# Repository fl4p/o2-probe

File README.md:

# o2-probe

A buried oxygen probe for compost windrows. It combines an electrochemical
O₂ cell, its potentiostat, a heated membrane, and an STM32 that speaks
Modbus RTU, all on one elongated PCB inside a printed body that is potted at
one end and open to the pile gas at the other.

Measuring O₂ in a pile is mainly a condensation problem. Pore gas is
saturated and a buried probe conducts heat outward, so every surface sits
below the dew point. The cell, however, is rated 15–90 %RH *non-condensing*.
Most of this design exists to keep the membrane dry.

*Right: the assembled probe, with half of the printed one-piece body (the
"monobody") cut away. The board is the 107 mm Rev A layout, as KiCad
exports it in 3D. Parts with no KiCad 3D model are red blocks drawn in by
hand. The cable-end cap is at the bottom. Rebuild it with
`make -C cad readme-render`.*

**View the board in the browser:**
[Rev B PCB and schematic in KiCanvas](https://kicanvas.org/?github=https%3A%2F%2Fgithub.com%2Ffl4p%2Fo2-probe%2Ftree%2Fmain%2Fhw%2Frouting%2Frevb-86)

## Status

Research hardware, not a product. A Rev A board runs on the bench and has
been in a pile. Rev B (20 × 86 mm, 2 layers, the ADS1119 replaced by the
STM32's own ADC) is routed and reviewed but not yet fabricated.
`hw/README.md` has the current board state.

## Layout

| path | contents |
|---|---|
| `hw/` | electronics: the KiCad project, its generators (`gen_sch.py` is the schematic's source of truth), audits, routing variants, fab packages, bench logs |
| `hw/firmware/` | STM32G071 firmware (PlatformIO). Its scale factors are generated from `../gen_sch.py` |
| `cad/` | the printed body, head end and fixtures (OpenSCAD), print profiles, the three.js viewer |
| `docs/` | system-level design records: membrane, potting, power, cable, condensation model, calibration budget |
| `model/` | lumped response and heater model (Python, uncalibrated) |
| `analysis/` | calibration and field-error budget scripts |
| `reviews/` | independent design reviews |
| `vendor/` | vendor documents for the membrane |
| `viewer/` | superseded Rev A three.js viewer |

## Where to start

- `docs/PLAN.md` is the system plan and indexes the other design records.
- `hw/DESIGN.md` covers the architecture, I²C address map, register map and
  release gates.
- `hw/firmware/FIRMWARE.md` covers the register map, fault semantics and
  bring-up.
- `docs/O2-CORRECTION-MODEL-BUDGET.md` shows what calibration can and cannot
  buy.
- `cad/README.md` covers the mechanical parts and how to build them.

## History

The electronics and firmware were developed in a separate monorepo and moved
here on 2026-11-02 with their history intact (`hw/`). Before that, this repo's
root held an older, frozen copy of the KiCad project. That copy was removed,
and git history still has it.

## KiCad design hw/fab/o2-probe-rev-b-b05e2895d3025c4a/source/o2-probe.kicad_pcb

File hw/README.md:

# o2-probe

Current Rev B PCB work is in
[`routing/revb-86/o2-probe.kicad_pcb`](routing/revb-86/o2-probe.kicad_pcb).
It uses the current 83-component schematic: AP63203 supplies 3.3 V, R32 filters
the analog rail, REF3425 supplies the reference, and the STM32 ADC replaces
ADS1119. The outline is 20 × 86 mm on two copper layers with a 1.6 mm nominal
board target. J5 and the external heated ring remain
[deferred Rev C work](plans/REVC-HEATED-RING.md).

The cable-end trim removes 3 mm from the accepted 89 mm board while retaining every component, hole, track, via and thermal slot. The PCB is complete and [independently reviewed](docs/2026-09-12-revb-86-review.md): native 0 errors, 0 unconnected items and 0 schematic mismatches, with 195 vias. The ten assembly courtyard and two intentional guard-endpoint warnings remain visible and individually documented.

[86 mm fabrication package](fab/o2-probe-revb-86-4837fd61405f8b2b/o2-probe-revb-86.zip) · [artifact review](docs/2026-09-12-revb-86-artifact-review.md) · [archived implementation plan](docs/archive/2026-09-12-pcb-plans/REVB-AISLER.md). This uses the user-overridden 0.10 mm trace/spacing and 0.20 mm via-drill profile; it is not a standard-Aisler-compliance claim. Procurement and first-article electrical, thermal and mechanical qualification remain open.

The accepted [89 mm board](routing/revb-current/o2-probe.kicad_pcb) and [89 mm package](fab/o2-probe-revb-current-8eef4aa26e24a6cb/o2-probe-revb-current.zip) remain available as the previous revision.

A buried oxygen probe for compost windrows: an electrochemical cell, its
potentiostat, a heated membrane, and an STM32 that speaks Modbus RTU, on one
elongated PCB that is potted at one end and breathing at the other.

It exists because measuring O₂ in a pile is not a sensor problem, it is a
condensation problem. Pore gas is saturated, a buried probe conducts heat
outward, and every surface therefore sits below the dew point — while the cell
is rated 15–90 %RH *non-condensing*. So the board carries a heated membrane
ring, and the firmware's job is as much keeping the membrane dry as reading
the cell.

Hardware and firmware live together here because they are one contract: the
firmware's scale factors are **generated** from the schematic (see
[The hardware contract](#the-hardware-contract)).

## Rev A status snapshot, 2026-09-05

**Bare-board first article. Not qualified, not deployed, not potted.**

| | |
|---|---|
| Schematic / PCB | released for a bare-board first article; ERC and DRC clean |
| Firmware v0 | builds, 49 host tests pass — **has never run on hardware** |
| Firmware v1 image | **runs on hardware** (2026-09-05): answers Modbus FC03, publishes T/RH and the diagnostic block |
| Firmware v1 heater loop | implemented and **shipped disabled**, pending the TMP117 alert fault test |
| Cell fit, enclosure fit, potting | unqualified; physical sample gates open. Two new SGX cells arrived 2026-09-05, so the air/nitrogen pair and the bias-plateau sweep are runnable again |
| RS-485 bootloader | **exists and is demonstrated** (2026-09-05): two images staged, CRC-verified and installed over the bus, `UPD_INSTALLS` 0 → 2 |

Two consequences worth stating plainly:

- **Do not pot a probe** — but the reason has narrowed. The application
  bootloader now works: on 2026-09-05 a 26,664-byte image was staged and
  installed over RS-485 twice, and the probe came back answering. What remains
  is recovery, not update: J3 is not exposed through the enclosure, so a potted
  board whose *bootloader* is the thing that breaks has no way back. Today's
  session is the standing argument for caring — the bench bridge spent the
  evening in its ROM bootloader because SWCLK doubles as BOOT0, and SWD was the
  only way out (`~/dev/kb/tooling/probe-swclk-pullup-straps-stm32-boot0.md`).
  `SCHEMATIC-REVIEW.md` M2 has the rest of the detail.
- **Do not bury one running v0.** v0 ships the membrane heater hard-disabled,
  pending a fault test of the TMP117 alert cutoff — which means nothing is
  holding the membrane above the dew point. It is a bench and short-trial
  build. `firmware/FIRMWARE.md` says so in more detail.

## Rev A signal chain

```
SGX-OX-ROHS-Mini ──▶ LMP91000 ──▶ ADS1119 ──▶ STM32G071CBT7 ──▶ THVD1410 ──▶ RS-485
 biased 3-electrode  potentiostat  16-bit ADC   Cortex-M0+,        half duplex
 cell, −600 mV,      7 kΩ TIA,     ratiometric  Modbus RTU slave
 0.1 mA in air       67 % zero     to VREF      9600 8E1
```

Alongside: a TMP117 at the warm tip whose alert pin is wired straight to the
heater MOSFET gate as a hardware cutoff, an SHT45 as the condensation-margin
channel, and two 280 Ω resistors driving a soldered membrane-carrier ring
(140 Ω, 1.03 W at 12 V).

One four-wire farm cable does everything — brown +12 V, white GND, green A,
yellow B — over a 7–15 V input. The bus is shared with two Truebner SMT100
soil probes and a Dragino RS485-LS acting as LoRaWAN master.

The board is 20.0 × 107.0 mm, two layers on a 1.0 mm stack, split by a potting
datum at y = 82 mm with a thermal break beyond it so the gas-side tip can be
heated without heating the whole probe.

## Layout

```
*.kicad_sch  *.kicad_pcb   the KiCad project — GENERATED, see below
gen_sch.py   gen_pcb.py    the generators that are the actual source of truth
audit_*.py                 machine-enforced design rules, with --calibrate
DESIGN.md                  the design record: architecture, address map, gates
firmware/                  STM32G071 firmware, PlatformIO + STM32Cube
lib/                       project-local symbols and footprints
```

`gen_sch.py` is the source of truth for the schematic. **Do not hand-edit
`o2-probe.kicad_sch`** — change the generator and regenerate.

## Building the firmware

```sh
cd firmware
pio test -e native      # portable logic on the host
pio run  -e o2probe     # cross build
pio run  -e o2probe -t upload
```

Flashing is pre-pot only, over the J3 Tag-Connect footprint (TC2030-IDC-NL-6),
using any ST-LINK — including the one on a Nucleo board in external-target
mode. J3 pin 1 is VTREF, not a supply: power the board from its 12 V feed.

## Regenerating the hardware

```sh
python3 gen_sch.py
kicad-cli sch erc --exit-code-violations -o erc.rpt o2-probe.kicad_sch
python3 audit_schematic.py
```

`DESIGN.md` carries the full sequence including the PCB side.

## The hardware contract

The firmware converts ADC codes with divider ratios that live in the
schematic. Those have already moved once — the input-voltage divider went from
130k/20k to 82k/10k — and nothing but a comment connected the two.

So `firmware/tools/gen_hw_contract.py` imports `gen_sch.py`, extracts every
value the firmware converts with, and writes `firmware/src/hw_contract.h`. A
PlatformIO pre-build action regenerates and diffs it, and `board_pins.h`
static-asserts each GPIO binding against the generated pin map. A schematic
change that rescales a divider or moves a pin now **breaks the build** instead
of silently rescaling every reported value.

```sh
cd firmware
python3 tools/gen_hw_contract.py          # regenerate after a schematic change
python3 tools/gen_hw_contract.py --check  # what the build runs
python3 tools/check_regmap_docs.py        # prose register map vs regmap.h
```

## Further reading

| | |
|---|---|
| `DESIGN.md` | architecture, I²C address map, register map, release gates |
| `firmware/FIRMWARE.md` | register map, fault semantics, bring-up procedure |
| `SCHEMATIC-REVIEW.md` | review findings M1–M4 and their closures |
| `FAB-READINESS.md` | what must pass before fabrication and assembly |
| `THERMAL-BARRIER.md` | the ~98 K/W tip isolation, the heater's plant model |
| `PLACEMENT.md`, `ROUTING.md` | layout constraints and their rationale |

Selection rationale, the condensation model and the membrane study live in the
separate compostlab `o2-probe` planning repository.

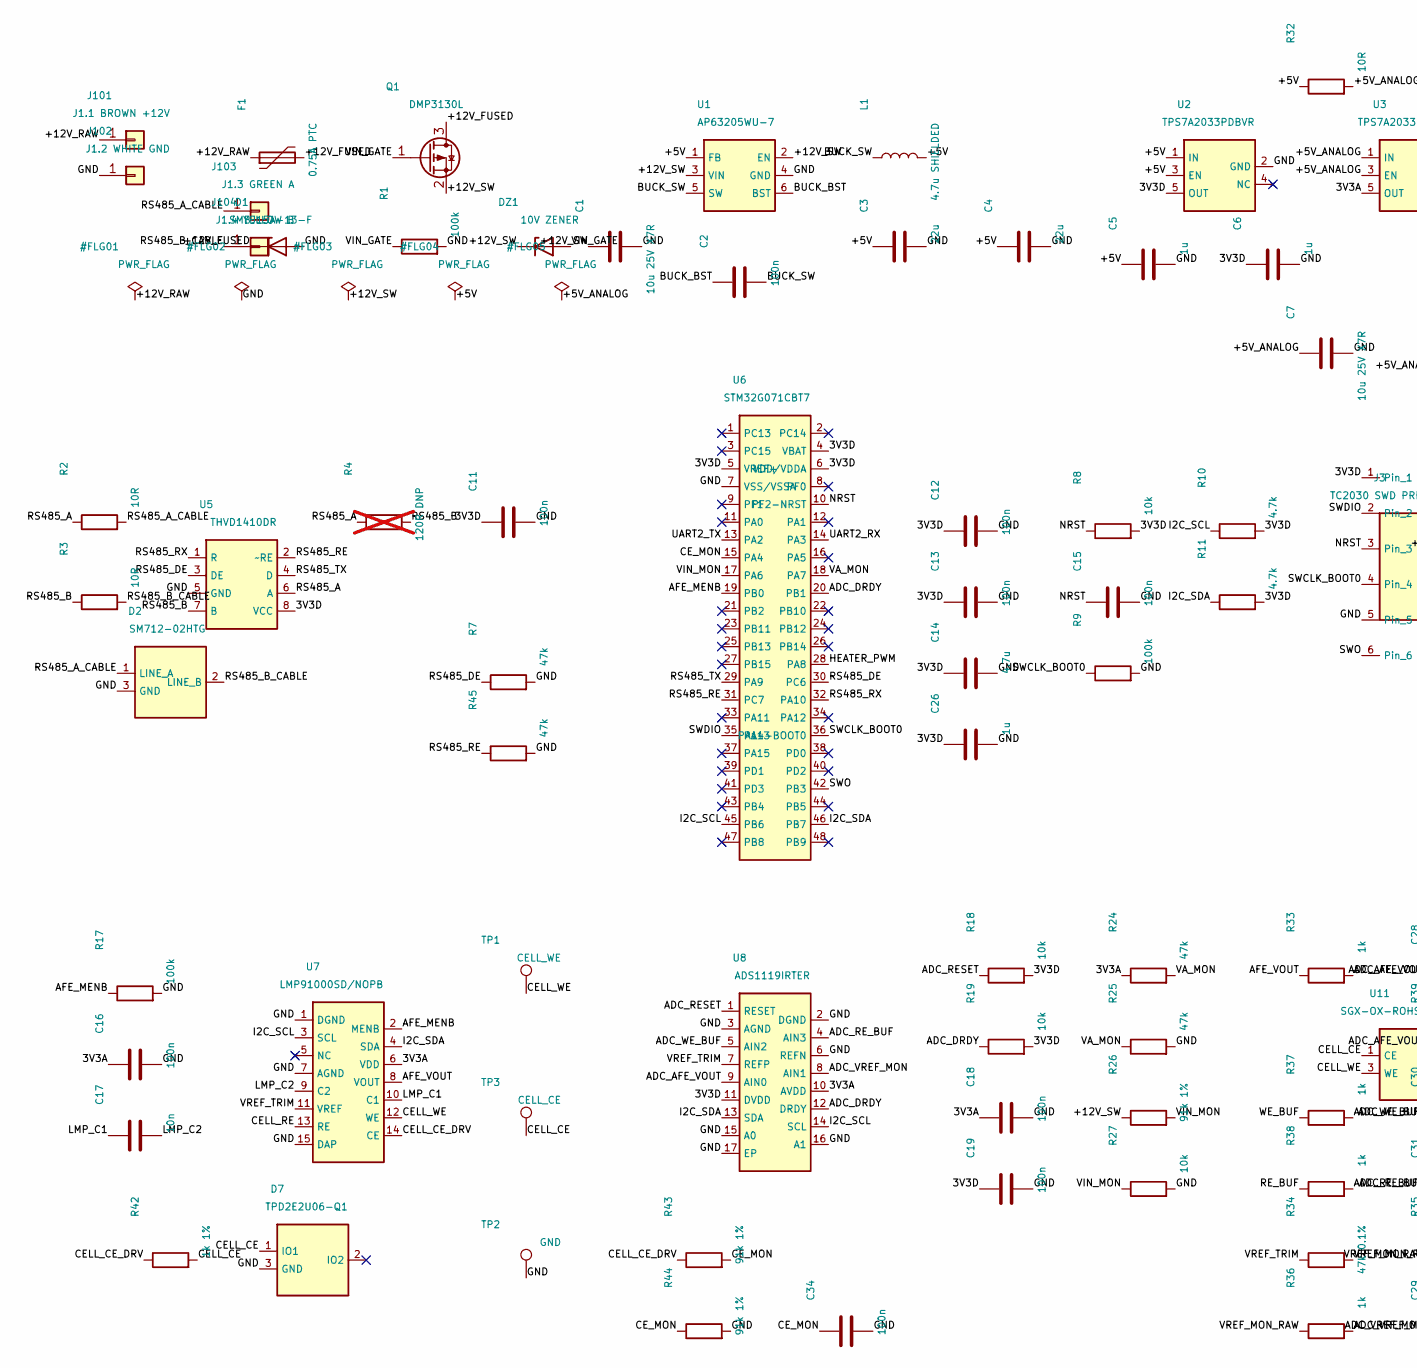
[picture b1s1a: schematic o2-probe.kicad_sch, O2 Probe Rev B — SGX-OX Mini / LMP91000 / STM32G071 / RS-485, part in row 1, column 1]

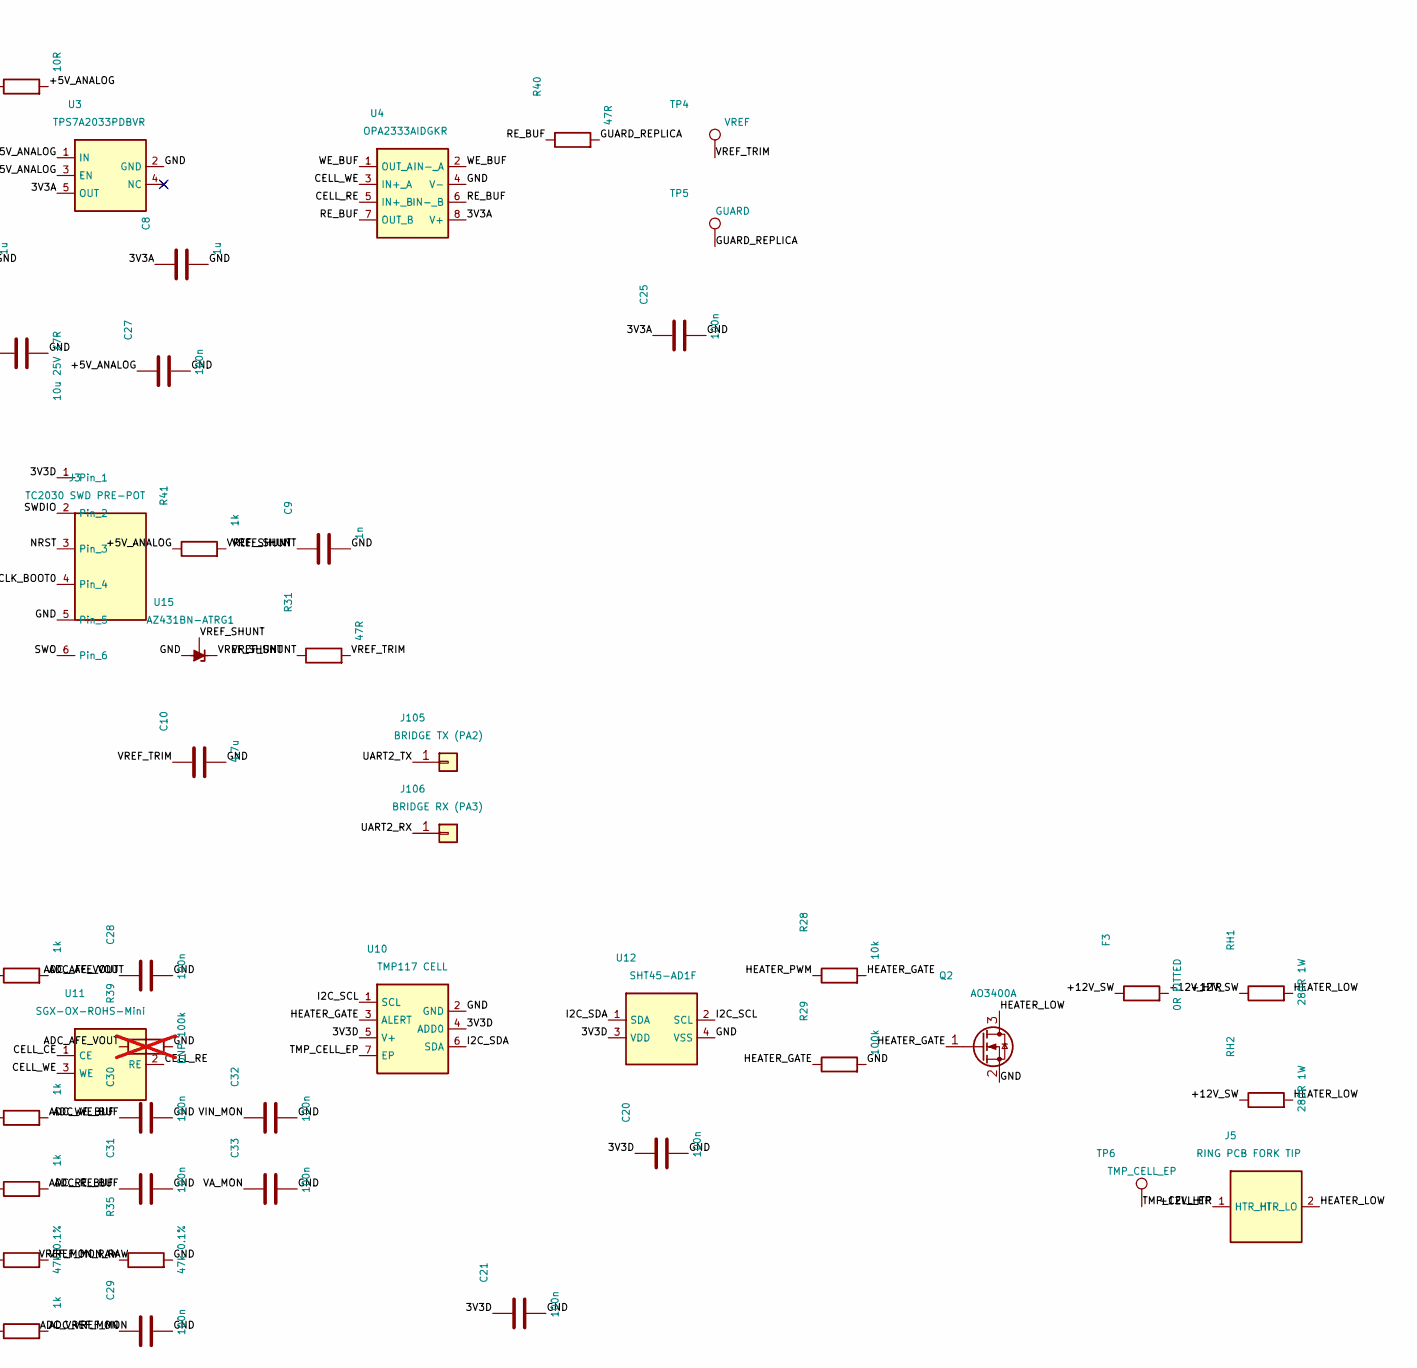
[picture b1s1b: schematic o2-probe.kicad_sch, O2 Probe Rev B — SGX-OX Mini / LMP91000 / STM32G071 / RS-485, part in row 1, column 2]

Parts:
C1, C7: 10u 25V X7R; C_1206_3216Metric
C2, C11, C12, C13, C15, C16, C18, C19, C20, C21, C25, C27, C28, C29, C30, C31, C32, C33, C34: 100n; C_0402_1005Metric
C3, C4: 22u; C_1206_3216Metric
C5, C6, C8, C26: 1u; C_0603_1608Metric
C9: 1n; C_0603_1608Metric
C10, C14: 4.7u; C_0603_1608Metric
C17: 10n; C_0603_1608Metric
D1: SMBJ15A-13-F; D_SMB; MPN SMBJ15A-13-F
D2: SM712-02HTG; SOT-23; MPN SM712-02HTG
D7: TPD2E2U06-Q1; SOT-23; MPN TPD2E2U06QDBZRQ1
DZ1: 10V ZENER; D_SOD-123; MPN BZT52C10-E3-08
F1: 0.75A PTC; PTC_1206_3216Metric; MPN 0ZCJ0075AF2E
F3: 0R FITTED; R_0603_1608Metric
J3: TC2030 SWD PRE-POT; Tag-Connect_TC2030-IDC-NL_2x03_P1.27mm_Vertical
J5: RING PCB FORK TIP; Ring_Fork_Tip_DRAFT
J101: J1.1 BROWN +12V; SolderWire-0.25sqmm_1x01_D0.65mm_OD1.7mm_Relief
J102: J1.2 WHITE GND; SolderWire-0.25sqmm_1x01_D0.65mm_OD1.7mm_Relief
J103: J1.3 GREEN A; SolderWire_RaisedRelief_1x01
J104: J1.4 YELLOW B; SolderWire_RaisedRelief_1x01
J105: BRIDGE TX (PA2); SolderWireNoRelief_J105
J106: BRIDGE RX (PA3); SolderWireNoRelief_J106
L1: 4.7u SHIELDED; L_6.3x6.3_H3; MPN SRN6028C-4R7M
Q1: DMP3130L; SOT-23; MPN DMP3130L-7
Q2: AO3400A; SOT-23; MPN AO3400A
R1, R9, R17, R29: 100k; R_0603_1608Metric
R2, R3, R32: 10R; R_0603_1608Metric
R4: 120R DNP; R_0603_1608Metric; not fitted
R7, R24, R25, R45: 47k; R_0603_1608Metric
R8, R18, R19, R27, R28: 10k; R_0603_1608Metric
R10, R11: 4.7k; R_0603_1608Metric
R26, R43, R44: 91k 1%; R_0603_1608Metric; MPN RC0603FR-0791KL
R31, R40: 47R; R_0603_1608Metric
R33, R36, R37, R38, R41: 1k; R_0603_1608Metric
R34, R35: 47k 0.1%; R_0603_1608Metric; MPN RT0603BRD0747KL
R39: DNP 100k; R_0603_1608Metric; not fitted
R42: 1k 1%; R_0603_1608Metric; MPN RC0603FR-071KL
RH1, RH2: 280R 1W; R_2512_6332Metric; MPN CRCW2512280RFKEG
TP1: CELL_WE; TestPoint_Pad_D1.0mm
TP2: GND; TestPoint_Pad_D1.0mm
TP3: CELL_CE; TestPoint_Pad_D1.0mm
TP4: VREF; TestPoint_Pad_D1.0mm
TP5: GUARD; TestPoint_Pad_D1.0mm
TP6: TMP_CELL_EP; TestPoint_Pad_D1.0mm
U1: AP63205WU-7; TSOT-23-6; MPN AP63205WU-7
U2, U3: TPS7A2033PDBVR; SOT-23-5; MPN TPS7A2033PDBVR
U4: OPA2333AIDGKR; VSSOP-8_3x3mm_P0.65mm; MPN OPA2333AIDGKR
U5: THVD1410DR; SOIC-8_3.9x4.9mm_P1.27mm; MPN THVD1410DR
U6: STM32G071CBT7; LQFP-48_7x7mm_P0.5mm; MPN STM32G071CBT7
U7: LMP91000SD/NOPB; WSON-14-1EP_4.0x4.0mm_P0.5mm_EP2.6x2.6mm; MPN LMP91000SDX/NOPB
U8: ADS1119IRTER; Texas_RTE0016D_WQFN-16-1EP_3x3mm_P0.5mm_EP0.8x0.8mm; MPN ADS1119IRTER
U10: TMP117 CELL; TMP117_WSON-6-1EP_2x2mm_TI; MPN TMP117AIDRVR
U11: SGX-OX-ROHS-Mini; SGX-OX-ROHS-Mini_ISS2; MPN SGX-OX-ROHS-Mini
U12: SHT45-AD1F; Sensirion_DFN-4_1.5x1.5mm_P0.8mm_SHT4x_NoCentralPad; MPN SHT45-AD1F-R2
U15: AZ431BN-ATRG1; SOT-23; MPN AZ431BN-ATRG1

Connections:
/3V3A: C8.1, C16.1, C18.1, C25.1, R24.1, U3.5 (OUT), U4.8 (V+), U7.6 (VDD), U8.10 (AVDD)
/3V3D: C6.1, C11.1, C12.1, C13.1, C14.1, C19.1, C20.1, C21.1, C26.1, J3.1, R8.2, R10.2, R11.2, R18.2, R19.2, U2.5 (OUT), U5.8 (VCC), U6.4 (VBAT), U6.5 (VREF+), U6.6 (VDD/VDDA), U8.11 (DVDD), U10.4 (ADD0), U10.5 (V+), U12.3 (VDD)
/+5V: C3.1, C4.1, C5.1, L1.2, R32.1, U1.1 (FB), U2.1 (IN), U2.3 (EN)
/+5V_ANALOG: C7.1, C27.1, R32.2, R41.1, U3.1 (IN), U3.3 (EN)
/+12V_FUSED: D1.1 (K), F1.2, Q1.3 (D)
/+12V_HTR: F3.2, J5.1 (HTR_HI)
/+12V_RAW: F1.1, J101.1
/+12V_SW: C1.1, DZ1.1 (K), F3.1, Q1.2 (S), R26.1, RH1.1, RH2.1, U1.2 (EN), U1.3 (VIN)
/ADC_AFE_VOUT: C28.1, R33.2, R39.1, U8.9 (AIN0)
/ADC_DRDY: R19.1, U6.20 (PB1), U8.12 (DRDY)
/ADC_RESET: R18.1, U8.1 (RESET)
/ADC_RE_BUF: C31.1, R38.2, U8.4 (AIN3)
/ADC_VREF_MON: C29.1, R36.2, U8.8 (AIN1)
/ADC_WE_BUF: C30.1, R37.2, U8.5 (AIN2)
/AFE_MENB: R17.1, U6.19 (PB0), U7.2 (MENB)
/AFE_VOUT: R33.1, U7.8 (VOUT)
/BUCK_BST: C2.1, U1.6 (BST)
/BUCK_SW: C2.2, L1.1, U1.5 (SW)
/CELL_CE: D7.1 (IO1), R42.2, TP3.1, U11.1 (CE)
/CELL_CE_DRV: R42.1, R43.1, U7.14 (CE)
/CELL_RE: U4.5 (IN+_B), U7.13 (RE), U11.2 (RE)
/CELL_WE: TP1.1, U4.3 (IN+_A), U7.12 (WE), U11.3 (WE)
/CE_MON: C34.1, R43.2, R44.1, U6.15 (PA4)
/GND: C1.2, C3.2, C4.2, C5.2, C6.2, C7.2, C8.2, C9.2, C10.2, C11.2, C12.2, C13.2, C14.2, C15.2, C16.2, C18.2, C19.2, C20.2, C21.2, C25.2, C26.2, C27.2, C28.2, C29.2, C30.2, C31.2, C32.2, C33.2, C34.2, D1.2 (A), D2.3 (GND), D7.3 (GND), J3.5, J102.1, Q2.2 (S), R1.2, R7.2, R9.2, R17.2, R25.2, R27.2, R29.2, R35.2, R39.2, R44.2, R45.2, TP2.1, U1.4 (GND), U2.2 (GND), U3.2 (GND), U4.4 (V-), U5.5 (GND), U6.7 (VSS/VSSA), U7.1 (DGND), U7.7 (AGND), U7.15 (DAP), U8.2 (DGND), U8.3 (AGND), U8.6 (REFN), U8.15 (A0), U8.16 (A1), U8.17 (EP), U10.2 (GND), U12.4 (VSS), U15.3 (A)
/GUARD_REPLICA: R40.2, TP5.1
/HEATER_GATE: Q2.1 (G), R28.2, R29.1, U10.3 (ALERT)
/HEATER_LOW: J5.2 (HTR_LO), Q2.3 (D), RH1.2, RH2.2
/HEATER_PWM: R28.1, U6.28 (PA8)
/I2C_SCL: R10.1, U6.45 (PB6), U7.3 (SCL), U8.14 (SCL), U10.1 (SCL), U12.2 (SCL)
/I2C_SDA: R11.1, U6.46 (PB7), U7.4 (SDA), U8.13 (SDA), U10.6 (SDA), U12.1 (SDA)
/LMP_C1: C17.1, U7.10 (C1)
/LMP_C2: C17.2, U7.9 (C2)
/NRST: C15.1, J3.3, R8.1, U6.10 (PF2-NRST)
/RE_BUF: R38.1, R40.1, U4.6 (IN-_B), U4.7 (OUT_B)
/RS485_A: R2.1, R4.1, U5.6 (A)
/RS485_A_CABLE: D2.1 (LINE_A), J103.1, R2.2
/RS485_B: R3.1, R4.2, U5.7 (B)
/RS485_B_CABLE: D2.2 (LINE_B), J104.1, R3.2
/RS485_DE: R7.1, U5.3 (DE), U6.30 (PC6)
/RS485_RE: R45.1, U5.2 (~RE), U6.31 (PC7)
/RS485_RX: U5.1 (R), U6.32 (PA10)
/RS485_TX: U5.4 (D), U6.29 (PA9)
/SWCLK_BOOT0: J3.4, R9.1, U6.36 (PA14-BOOT0)
/SWDIO: J3.2, U6.35 (PA13)
/SWO: J3.6, U6.42 (PB3)
/TMP_CELL_EP: TP6.1, U10.7 (EP)
/UART2_RX: J106.1, U6.14 (PA3)
/UART2_TX: J105.1, U6.13 (PA2)
/VA_MON: C33.1, R24.2, R25.1, U6.18 (PA7)
/VIN_GATE: DZ1.2 (A), Q1.1 (G), R1.1
/VIN_MON: C32.1, R26.2, R27.1, U6.17 (PA6)
/VREF_MON_RAW: R34.2, R35.1, R36.1
/VREF_SHUNT: C9.1, R31.1, R41.2, U15.1 (REF), U15.2 (K)
/VREF_TRIM: C10.1, R31.2, R34.1, TP4.1, U7.11 (VREF), U8.7 (REFP)
/WE_BUF: R37.1, U4.1 (OUT_A), U4.2 (IN-_A)

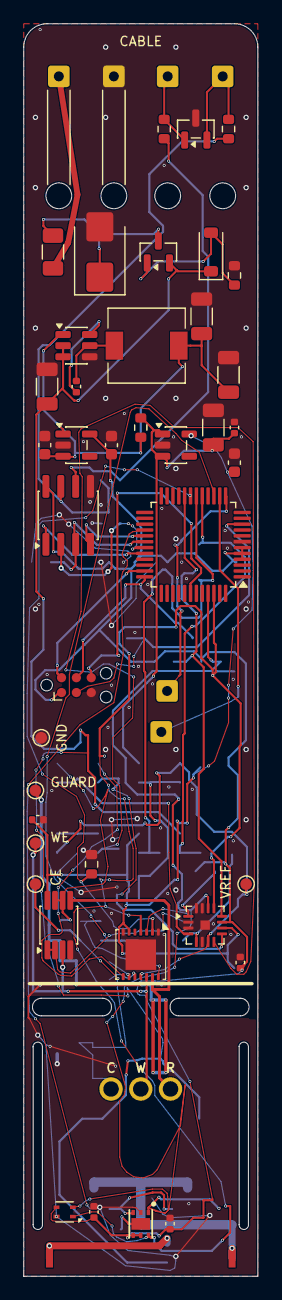
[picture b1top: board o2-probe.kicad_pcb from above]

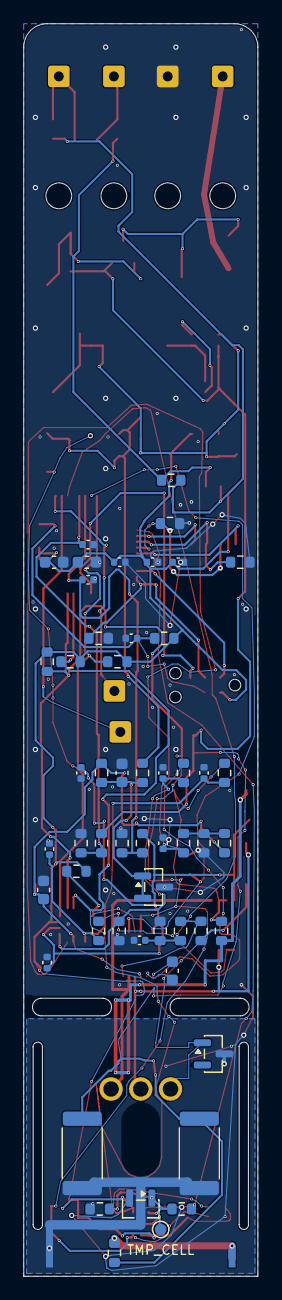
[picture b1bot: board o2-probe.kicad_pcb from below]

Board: 2 copper layers, 20.0 x 107.0 mm, 101 parts (55 on the bottom side), 55 nets.

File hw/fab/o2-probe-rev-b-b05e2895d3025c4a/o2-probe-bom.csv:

mpn,value,footprint,qty_per_board,fitted,sourcing,refs
,0R FITTED,Resistor_SMD:R_0603_1608Metric,1,yes,unsourced,F3
,10u 25V X7R,Capacitor_SMD:C_1206_3216Metric,2,yes,unsourced,C1 C7
,1n,Capacitor_SMD:C_0603_1608Metric,1,yes,unsourced,C9
,RING PCB FORK TIP,o2-probe:Ring_Fork_Tip_DRAFT,1,yes,unsourced,J5
,TC2030 SWD PRE-POT,Connector:Tag-Connect_TC2030-IDC-NL_2x03_P1.27mm_Vertical,1,yes,unsourced,J3
,120R DNP,Resistor_SMD:R_0603_1608Metric,0,no,dnp,R4
,DNP 100k,Resistor_SMD:R_0603_1608Metric,0,no,dnp,R39
,100k,Resistor_SMD:R_0603_1608Metric,4,yes,generic-stock,R1 R17 R29 R9
,100n,Capacitor_SMD:C_0402_1005Metric,19,yes,generic-stock,C11 C12 C13 C15 C16 C18 C19 C2 C20 C21 C25 C27 C28 C29 C30 C31 C32 C33 C34
,10R,Resistor_SMD:R_0603_1608Metric,3,yes,generic-stock,R2 R3 R32
,10k,Resistor_SMD:R_0603_1608Metric,5,yes,generic-stock,R18 R19 R27 R28 R8
,10n,Capacitor_SMD:C_0603_1608Metric,1,yes,generic-stock,C17
,1k,Resistor_SMD:R_0603_1608Metric,5,yes,generic-stock,R33 R36 R37 R38 R41
,1u,Capacitor_SMD:C_0603_1608Metric,4,yes,generic-stock,C26 C5 C6 C8
,22u,Capacitor_SMD:C_1206_3216Metric,2,yes,generic-stock,C3 C4
,4.7k,Resistor_SMD:R_0603_1608Metric,2,yes,generic-stock,R10 R11
,4.7u,Capacitor_SMD:C_0603_1608Metric,2,yes,generic-stock,C10 C14
,47R,Resistor_SMD:R_0603_1608Metric,2,yes,generic-stock,R31 R40
,47k,Resistor_SMD:R_0603_1608Metric,4,yes,generic-stock,R24 R25 R45 R7
0ZCJ0075AF2E,0.75A PTC,o2-probe:PTC_1206_3216Metric,1,yes,mpn,F1
ADS1119IRTER,ADS1119IRTER,Package_DFN_QFN:Texas_RTE0016D_WQFN-16-1EP_3x3mm_P0.5mm_EP0.8x0.8mm,1,yes,mpn,U8
AO3400A,AO3400A,Package_TO_SOT_SMD:SOT-23,1,yes,mpn,Q2
AP63205WU-7,AP63205WU-7,Package_TO_SOT_SMD:TSOT-23-6,1,yes,mpn,U1
AZ431BN-ATRG1,AZ431BN-ATRG1,Package_TO_SOT_SMD:SOT-23,1,yes,mpn,U15
BZT52C10-E3-08,10V ZENER,Diode_SMD:D_SOD-123,1,yes,mpn,DZ1
CRCW2512280RFKEG,280R 1W,Resistor_SMD:R_2512_6332Metric,2,yes,mpn,RH1 RH2
DMP3130L-7,DMP3130L,Package_TO_SOT_SMD:SOT-23,1,yes,mpn,Q1
LMP91000SDX/NOPB,LMP91000SD/NOPB,Package_SON:WSON-14-1EP_4.0x4.0mm_P0.5mm_EP2.6x2.6mm,1,yes,mpn,U7
OPA2333AIDGKR,OPA2333AIDGKR,Package_SO:VSSOP-8_3x3mm_P0.65mm,1,yes,mpn,U4
RC0603FR-071KL,1k 1%,Resistor_SMD:R_0603_1608Metric,1,yes,mpn,R42
RC0603FR-0791KL,91k 1%,Resistor_SMD:R_0603_1608Metric,3,yes,mpn,R26 R43 R44
RT0603BRD0747KL,47k 0.1%,Resistor_SMD:R_0603_1608Metric,2,yes,mpn,R34 R35
SGX-OX-ROHS-Mini,SGX-OX-ROHS-Mini,o2-probe:SGX-OX-ROHS-Mini_ISS2,1,yes,mpn,U11
SHT45-AD1F-R2,SHT45-AD1F,Sensor_Humidity:Sensirion_DFN-4_1.5x1.5mm_P0.8mm_SHT4x_NoCentralPad,1,yes,mpn,U12
SM712-02HTG,SM712-02HTG,Package_TO_SOT_SMD:SOT-23,1,yes,mpn,D2
SMBJ15A-13-F,SMBJ15A-13-F,Diode_SMD:D_SMB,1,yes,mpn,D1
SRN6028C-4R7M,4.7u SHIELDED,Inductor_SMD:L_6.3x6.3_H3,1,yes,mpn,L1
STM32G071CBT7,STM32G071CBT7,Package_QFP:LQFP-48_7x7mm_P0.5mm,1,yes,mpn,U6
THVD1410DR,THVD1410DR,Package_SO:SOIC-8_3.9x4.9mm_P1.27mm,1,yes,mpn,U5
TMP117AIDRVR,TMP117 CELL,tmp117-probe:TMP117_WSON-6-1EP_2x2mm_TI,1,yes,mpn,U10
TPD2E2U06QDBZRQ1,TPD2E2U06-Q1,Package_TO_SOT_SMD:SOT-23,1,yes,mpn,D7
TPS7A2033PDBVR,TPS7A2033PDBVR,Package_TO_SOT_SMD:SOT-23-5,2,yes,mpn,U2 U3
,BRIDGE RX (PA3),o2-probe:SolderWireNoRelief_J106,1,yes,not-purchased,J106
,BRIDGE TX (PA2),o2-probe:SolderWireNoRelief_J105,1,yes,not-purchased,J105
,CELL_CE,TestPoint:TestPoint_Pad_D1.0mm,1,yes,not-purchased,TP3
,CELL_WE,TestPoint:TestPoint_Pad_D1.0mm,1,yes,not-purchased,TP1
,GND,TestPoint:TestPoint_Pad_D1.0mm,1,yes,not-purchased,TP2
,GUARD,TestPoint:TestPoint_Pad_D1.0mm,1,yes,not-purchased,TP5
,J1.1 BROWN +12V,Connector_Wire:SolderWire-0.25sqmm_1x01_D0.65mm_OD1.7mm_Relief,1,yes,not-purchased,J101
,J1.2 WHITE GND,Connector_Wire:SolderWire-0.25sqmm_1x01_D0.65mm_OD1.7mm_Relief,1,yes,not-purchased,J102
,J1.3 GREEN A,o2-probe:SolderWire_RaisedRelief_1x01,1,yes,not-purchased,J103
,J1.4 YELLOW B,o2-probe:SolderWire_RaisedRelief_1x01,1,yes,not-purchased,J104
,TMP_CELL_EP,TestPoint:TestPoint_Pad_D1.0mm,1,yes,not-purchased,TP6
,VREF,TestPoint:TestPoint_Pad_D1.0mm,1,yes,not-purchased,TP4

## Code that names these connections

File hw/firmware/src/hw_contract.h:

/* GENERATED by tools/gen_hw_contract.py from ../gen_sch.py - DO NOT EDIT. */
/*
 * The schematic generator is this board's source of truth. Every constant
 * here is derived from it, so a hardware change that rescales a divider or
 * moves a pin fails the build rather than silently rescaling telemetry.
 * Regenerate with: python3 tools/gen_hw_contract.py
 */
#ifndef O2P_HW_CONTRACT_H
#define O2P_HW_CONTRACT_H

/* ---- STM32G071CBT7 LQFP-48 pin map (gen_sch.py MCU_NETS) ---- */
#define O2P_HW_PIN_04_NET "3V3D"
#define O2P_HW_PIN_05_NET "VREF_TRIM"
#define O2P_HW_PIN_06_NET "3V3D"
#define O2P_HW_PIN_07_NET "GND"
#define O2P_HW_PIN_10_NET "NRST"
#define O2P_HW_PIN_11_NET "ADC_WE_BUF"
#define O2P_HW_PIN_12_NET "ADC_RE_BUF"
#define O2P_HW_PIN_13_NET "UART2_TX"
#define O2P_HW_PIN_14_NET "UART2_RX"
#define O2P_HW_PIN_15_NET "CE_MON"
#define O2P_HW_PIN_17_NET "VIN_MON"
#define O2P_HW_PIN_18_NET "VA_MON"
#define O2P_HW_PIN_19_NET "AFE_MENB"
#define O2P_HW_PIN_20_NET "ADC_AFE_VOUT"
#define O2P_HW_PIN_28_NET "HEATER_PWM"
#define O2P_HW_PIN_29_NET "RS485_TX"
#define O2P_HW_PIN_30_NET "RS485_DE"
#define O2P_HW_PIN_31_NET "RS485_RE"
#define O2P_HW_PIN_32_NET "RS485_RX"
#define O2P_HW_PIN_35_NET "SWDIO"
#define O2P_HW_PIN_36_NET "SWCLK_BOOT0"
#define O2P_HW_PIN_42_NET "SWO"
#define O2P_HW_PIN_45_NET "I2C_SCL"
#define O2P_HW_PIN_46_NET "I2C_SDA"

#define O2P_HW_NET_3V3D_PIN 4
#define O2P_HW_NET_ADC_AFE_VOUT_PIN 20
#define O2P_HW_NET_ADC_RE_BUF_PIN 12
#define O2P_HW_NET_ADC_WE_BUF_PIN 11
#define O2P_HW_NET_AFE_MENB_PIN 19
#define O2P_HW_NET_CE_MON_PIN 15
#define O2P_HW_NET_GND_PIN 7
#define O2P_HW_NET_HEATER_PWM_PIN 28
#define O2P_HW_NET_I2C_SCL_PIN 45
#define O2P_HW_NET_I2C_SDA_PIN 46
#define O2P_HW_NET_NRST_PIN 10
#define O2P_HW_NET_RS485_DE_PIN 30
#define O2P_HW_NET_RS485_RE_PIN 31
#define O2P_HW_NET_RS485_RX_PIN 32
#define O2P_HW_NET_RS485_TX_PIN 29
#define O2P_HW_NET_SWCLK_BOOT0_PIN 36
#define O2P_HW_NET_SWDIO_PIN 35
#define O2P_HW_NET_SWO_PIN 42
#define O2P_HW_NET_UART2_RX_PIN 14
#define O2P_HW_NET_UART2_TX_PIN 13
#define O2P_HW_NET_VA_MON_PIN 18
#define O2P_HW_NET_VIN_MON_PIN 17
#define O2P_HW_NET_VREF_TRIM_PIN 5

/* ---- Resistive dividers the firmware converts with ---- */
/* MCU ADC1_IN6 (PA6) <- +12V_SW: R26 91000 / R27 10000 */
#define O2P_HW_DIV_VIN_NUM   10000
#define O2P_HW_DIV_VIN_DEN   101000
/* MCU ADC1_IN7 (PA7) <- 3V3A: R24 47000 / R25 27000 */
#define O2P_HW_DIV_VA_NUM    27000
#define O2P_HW_DIV_VA_DEN    74000
/* MCU ADC1_IN4 (PA4) <- CELL_CE_DRV (U7 pin 14): R43 91000 / R44 91000 */
#define O2P_HW_DIV_CE_NUM    91000
#define O2P_HW_DIV_CE_DEN    182000
/* CE fault-current limit, in the loop; scales nothing, bounds the budget. */
#define O2P_HW_CE_SERIES_OHM 1000
/* SNAS506 6.5 characterises A1's drive only over 300 mV <= VCE <= VS-300 mV.
 * Outside this the amplifier is simply not specified, so treat it as a
 * fault, not as a reading.  VS is 3V3A, whose WORST-CASE LOW corner is
 * 3234 mV (DESIGN.md), so the characterised ceiling is 2934 mV -- not the
 * 3000 mV this used to hard-code, which sat 66 mV outside the specified
 * range whenever the rail was at its low limit. */
#define O2P_HW_CE_COMPLIANCE_MIN_MV 300
#define O2P_HW_CE_COMPLIANCE_MAX_MV 2934
/* No guard divider: the guard is driven from the RE follower U4B through
 * R40, so it tracks the real electrode instead of a 0.909 x VREF replica. */

/* ---- Cell bias telemetry (ADS1119 AIN2/AIN3, differential) ---- */
/* CORRECTED 2026-09-04. The old note here claimed the bias step carries
 * +/-2 % of VREF, about +/-50 mV against a +/-10 mV cell window. That
 * misreads SNAS506I: the +/-2 % figure is Bias Programming RESOLUTION, not
 * accuracy. The accuracy parameter is VOS_RW, +/-1750 uV MAX at 24 % bias,
 * which is INSIDE the SGX window -- confirmed on the bench 2026-09-04 at
 * 597 mV measured against 598.56 mV commanded.
 * So this pair is not a trim aid and never was. It is an EXISTENCE check:
 * is the cell biased at all. On 2026-09-04 the LMP91000's control amplifier
 * A1 failed outright and no converter on the board could see it. Read
 * AIN2-AIN3 differentially, and compare against the COMMANDED bias with a
 * window -- a floating input converts cleanly and in range, so a clip check
 * does not catch it. */
#define O2P_HW_BIAS_ADC_CH_WE  2
#define O2P_HW_BIAS_ADC_CH_RE  3

/* ---- VREF: U15 AZ431B 2.5 V shunt reference, NOT adjustable ---- */
/* There is no trimmer. Firmware verifies the reference is within its own
 * guaranteed window and reports the measured cell bias separately; it can
 * neither set VREF nor correct the bias by moving it. */
#define O2P_HW_VREF_MIN_MV     2480
#define O2P_HW_VREF_MAX_MV     2520
#define O2P_HW_VREF_TARGET_MV  2500

/* ---- Membrane-ring heater ---- */
/* Main-board heater: RH1||RH2, bench-confirmed 140 ohm / 1.02 W at 12 V.
 * A ring PCB, when it exists, PARALLELS these through J5 -- it does not
 * replace them, so this is the floor of the load, not the whole of it. */
#define O2P_HW_HEATER_OHM    140
#define O2P_HW_HEATER_GATE_R_SERIES 10000   /* R28, PA8 -> gate */
#define O2P_HW_HEATER_GATE_R_PULLDN 100000   /* R29, passive default-off */

/* ---- I2C addresses, fixed by the strapping asserted above ---- */
#define O2P_HW_I2C_ADDR_ADS1119  0x40
#define O2P_HW_I2C_ADDR_SHT45    0x44
#define O2P_HW_I2C_ADDR_LMP91000 0x48
#define O2P_HW_I2C_ADDR_TMP117   0x49
#define O2P_HW_I2C_ADDR_TMP117_EXT 0x4A
#define O2P_HW_I2C_ADDR_BMP390   0x76  /* DNP */

#endif /* O2P_HW_CONTRACT_H */

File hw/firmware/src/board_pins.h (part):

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
/* --- Bindings ------------------------------------------------------------ */

/* RS-485, USART1. PA9/PA10 are USART1 TX/RX on AF1. */
#define O2P_RS485_TX_PORT     GPIOA
#define O2P_RS485_TX_PIN      9u
#define O2P_RS485_TX_AF       1u
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#define O2P_RS485_RX_PIN      10u
#define O2P_RS485_RX_AF       1u

/* Direction control. PC6 carries NO USART1_DE alternate function on this part
 * - it has only TIM2_CH3 (AF2) and TIM3_CH1 (AF1). USART1's hardware DE exists
 * only on PA12 and PB3, neither of which reaches the THVD1410. So DE is a
 * plain output driven in software; see modbus_rtu.c for the TC-interrupt
 * release. PLAN.md:261 says "USART+DE"; that is not achievable on this board.
 *
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 * drive it LOW to hear the bus, HIGH to deafen the receiver. On Rev A it was
 * shorted to DE, which made the part's 0.1 uA standby (/RE high, DE low)
 * uncommandable and left the receiver burning 700 uA forever - 24 % of the
 * whole board's idle draw (POWER-BUDGET.md). Rev B splits it onto PC7, the
 * package neighbour of PC6.
 *
 * PC7 carries no ADC channel - DS12232 Rev 1 Table 12 "Pin assignment and
 * description" leaves its "Additional functions" cell empty - so it cannot
 * collide with mcu_adc.c, and its only alternate functions are UCPD2_FRSTX,
 * TIM3_CH2 and TIM2_CH4, none of them used. Like DE it is a plain
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#define O2P_RS485_RE_PORT     GPIOC
#define O2P_RS485_RE_PIN      7u

/* The expansion/recovery UART, USART2. PA2/PA3 are USART2 TX/RX on AF1.
 *
 * NOTHING ON A SHIPPING PROBE USES THIS. Since 2026-09-05 these two pins land
 * on J105/J106, a pair of solder-wire lands, and stop there: the expansion
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#define O2P_EXP_UART_RX_PIN   3u
#define O2P_EXP_UART_RX_AF    1u

/* I2C1 on PB6/PB7, AF6. Bus is capped at 100 kHz because the LMP91000 is
 * standard-mode only (PLAN.md:234). 4.7k pull-ups are fitted (R10/R11). */
#define O2P_I2C_SCL_PORT      GPIOB
#define O2P_I2C_SCL_PIN       6u
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 * ready. There is no GPIO on the ADS1119 RESET pin - R18 holds it released and
 * recovery must go through the I2C RESET command.
 *
 * REV B DELETED THE ADS1119, and PB1 is now the AFE_VOUT ANALOG INPUT. Driving
 * it as a GPIO would configure the oxygen channel's own pin, so this block is
 * gated rather than left standing: on a board with no ADS1119 the symbols do
 * not exist and ads1119.c refuses to compile, instead of quietly reading DRDY
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#define O2P_ADC_DRDY_PIN      1u
#endif

/* Membrane-ring heater. PA8 is TIM1_CH1 on AF2.
 *
 * DANGER: PA7 is TIM1_CH1N, the complement of this very channel, and PA7 is
 * the analog rail monitor. TIM1 CH1N must never be enabled. See heater.c. */
#define O2P_HEATER_PWM_PORT   GPIOA
#define O2P_HEATER_PWM_PIN    8u
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 * names are asserted against the SCHEMATIC's pin map, so moving one of these
 * channels in gen_sch.py without moving mcu_adc.c breaks the build. Structure
 * matters here and is recorded where it is enforced: PA0/PA1 are the matched
 * FT_a pair carrying WE/RE, PA5 is the undivided /VREF_TRIM. */
O2P_ASSERT_NET(ADC_WE_BUF,   O2P_LQFP48_PA0);
O2P_ASSERT_NET(ADC_RE_BUF,   O2P_LQFP48_PA1);
/* ADOPTED 2026-09-12: /VREF_TRIM lands on VREF+ (pin 5), not on a channel. This
 * assertion is the firmware-side lock on the architecture -- if the schematic
 * ever puts pin 5 back on 3V3D, VDDA re-enters the oxygen derivation at
 * 0.718 mV/mV and the build stops instead of the readings quietly drifting. */
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 * o2p_modbus_rx_standby(true) would start DRIVING the shared cable while
 * trying to go deaf. */
_Static_assert(O2P_HW_NET_RS485_DE_PIN != O2P_HW_NET_RS485_RE_PIN,
               "RS485_DE and RS485_RE share an MCU pin again - the Rev B split is undone");

/* PA7 doubles as TIM1_CH1N for the PA8 heater channel. If a future schematic
 * moves the heater off TIM1, this pairing stops being a hazard and heater.c's
 * guard can be revisited - so pin it here too. */
_Static_assert(O2P_HW_NET_VA_MON_PIN == 18 && O2P_HW_NET_HEATER_PWM_PIN == 28,
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
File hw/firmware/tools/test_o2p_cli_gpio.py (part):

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    check(ok, "RDATA0 bit positions are gpio_diag.h's")

    print("resolving a pin")
    check(cli.resolve_gpio("PB3", names) == (1, 3) and cli.resolve_gpio("pb3", names) == (1, 3),
          "PB3, any case")
    check(cli.resolve_gpio("ADC_DRDY", names) == (1, 1) and
          cli.resolve_gpio("o2p_adc_drdy", names) == (1, 1), "a board_pins.h name, with or without O2P_")
    check(cli.resolve_gpio("PE3", names) == (4, 3) and cli.resolve_gpio("PB16", names) == (1, 16),
          "PE3 and PB16 are SENT, so the firmware's refusal is what the user sees")
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
    print("an analog pin is NOT SAMPLED, whatever its IDR bit says")
    for idr in (0x0002, 0x0000):
        code, text = h.run(["diag", "gpio", "ADC_DRDY"], setup=pin_setup(PORT["B"], 1, 3, idr=idr))
        reads = h.finish()
        pb1 = lines_for(text, "PB1")
        check(code == 0 and pb1 and "NOT SAMPLED" in pb1[0],
              "PB1 (ADC_DRDY) with IDR bit %d prints NOT SAMPLED" % (idr >> 1))
        check(not LEVEL_WORD.search(text), "and no HIGH or LOW anywhere in the output")
        check("analog" in text and reads[0] == 6, "the mode is still reported, from one snapshot")

    print("an input pin prints its real level, both ways")
    for idr, word in ((0x0002, "HIGH"), (0xFFFD, "LOW")):
        code, text = h.run(["diag", "gpio", "PB1"], setup=pin_setup(PORT["B"], 1, 0, idr=idr))
        h.finish()
        check(code == 0 and "PB1 (ADC_DRDY): %s" % word in text, "PB1 input, IDR %s -> %s" % (hex(idr), word))
        check(DRIVEN := cli.DRIVEN_NOT_REACHED not in text, "no drive warning on an input")
        del DRIVEN

    print("an output pin whose latch and level disagree is flagged")
    code, text = h.run(["diag", "gpio", "RS485_DE"],
                       setup=pin_setup(PORT["C"], 6, 1, odr=0x0040, idr=0x0000))
    h.finish()
    check("PC6 (RS485_DE): LOW" in text and "ODR    : 1" in text,
          "ODR 1 and IDR 0 are both printed as they are")
    check(cli.DRIVEN_NOT_REACHED in text, "and flagged: '%s'" % cli.DRIVEN_NOT_REACHED)
    code, text = h.run(["diag", "gpio", "PC6"], setup=pin_setup(PORT["C"], 6, 1, odr=0x0040, idr=0x0040))
    h.finish()
    check("HIGH" in text and cli.DRIVEN_NOT_REACHED not in text, "not flagged when they agree")
    code, text = h.run(["diag", "gpio", "PB6"],
                       setup=pin_setup(PORT["B"], 6, 1, od=1, odr=0x0040, idr=0x0000))
    h.finish()
    check(cli.DRIVEN_NOT_REACHED in text and "open-drain" in text,
          "an open-drain output released but held low says so")
    code, text = h.run(["diag", "gpio", "HEATER_PWM"],
                       setup=pin_setup(PORT["A"], 8, 2, af=2, odr=0x0000, idr=0x0100))
    h.finish()
    check(cli.DRIVEN_NOT_REACHED not in text and "AF2" in text,
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    print("walking a port")
    def port_b(link):
        moder = 0xFFFFFFFF
        moder = field(moder, 2, 0, 1)      # PB0 AFE_MENB output
        moder = field(moder, 2, 6, 2)      # PB6/PB7 I2C AF6, open-drain
        moder = field(moder, 2, 7, 2)
        set_port(link, PORT["B"], moder, 0x00C0, 0, 0x00C2, 0x0000, 0x66000000, 0)
    code, text = h.run(["diag", "gpio", "--port", "B"], setup=port_b)
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    h.finish()
    rows = [ln for ln in text.splitlines() if re.match(r"\s+PB\d+\s", ln)]
    check(params == [0x0100 + n for n in range(16)] and len(rows) == 16,
          "port B: one query per bonded pin, PB0..PB15, one row each")
    pb1 = lines_for(text, "PB1")
    check(pb1 and "NOT SAMPLED" in pb1[0] and not LEVEL_WORD.search(pb1[0]),
          "PB1's row is NOT SAMPLED, with no level")
    check(all(not LEVEL_WORD.search(r) for r in rows if "analog" in r),
          "no analog row carries a level")
    pb0 = lines_for(text, "PB0")
    check(pb0 and "output" in pb0[0] and "LOW" in pb0[0], "PB0 output row reads LOW")
    pb7 = lines_for(text, "PB7")
    check(pb7 and "AF6" in pb7[0] and "HIGH" in pb7[0] and "open-drain" in pb7[0],
          "PB7 (I2C_SDA) row: AF6, open-drain, HIGH")

    code, text = h.run(["diag", "gpio", "--port", "c"])
    params = gpio_writes(h.link)
    h.finish()
    check(params == [0x0206, 0x0207, 0x020D, 0x020E, 0x020F],
          "port C walks exactly PC6, PC7, PC13, PC14, PC15")

    code, text = h.run(["diag", "gpio", "--port", "D"])
    params = gpio_writes(h.link)
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
    code, text = "", ""
    try:
        h.run(["diag", "gpio", "PB1"], setup=pin_setup(PORT["B"], 1, 0, idr=2), before=peer)
        check(False, "a peer's command between write and read-back is refused")
    except cli.GpioTorn:
        check(not state["armed"], "a peer's command between write and read-back is refused")
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        return list(struct.unpack(">7H", rsp[3:17]))

    try:
        code, text = h.run(["diag", "gpio", "PB1"], setup=queue_lmp)
    except ModbusException as e:
        # The tool must report the refusal, not let it escape.
        code, text = "raised exception %d" % e.code, ""
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    reads = h.finish()
    check(code == 1 and "exception 06" in text and "busy" in text.lower() and
          not LEVEL_WORD.search(text),
          "master 2's `diag gpio PB1` is refused as busy, exit 1, no level")
    check(after[:3] == [0x5A01, 0x0010, cli.DIAG_PENDING],
          "and master 1's command still reads 0x5A01 0x0010 PENDING (%s)"
          % ["0x%04X" % v for v in after[:3]])
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    link = peek.OracleLink(exe)
    out = []
    rc = cli.cmd_diag_gpio(Bus(Refuse08(link), 3),
                           type("A", (), {"param": "PB1", "gpio_port": None})(), out=out.append)
    link.close()
    probe_fw = "FW_VERSION 0x%04X" % cli.FW_LATEST
    check(rc == 1 and any(probe_fw in ln and "needs 0x%04X" % cli.FW_READ_GPIO in ln
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    link = peek.OracleLink(exe)
    out = []
    try:
        rc = cli.cmd_diag_gpio(Bus(link, 3), type("A", (), {"param": "PB1", "gpio_port": None})(),
                               out=out.append)
        check(rc == 1 and any("exception 02" in ln for ln in out) and
              not any(LEVEL_WORD.search(ln) for ln in out),
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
